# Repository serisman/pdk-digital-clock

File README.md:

# pdk-digital-clock
A 4-digit 7-segment digital clock, based on the inexpensive 8-bit Padauk microcontrollers

This project uses the [SLR0394DRC5BD](https://lcsc.com/product-detail/Led-Segment-Display_SUNLIGHT-SLR0394DRA5BD_C225902.html) 4-digit 7-segment common cathode 'time' display,
which sits over the top of a 74HC595 and (2) 4x resistor packs.
The 74HC595 is used to enable each of the four 7-segment digits, one at a time, using two output pins per digit for extra current sink capabilities.
The segments themselves are driven directly by the Port B outputs of the Padauk microcontroller.
Each of the four 7-segment digits is enabled and updated, one at a time, several 10's of times a second.

### Default Firmware (Push Button)
- Link: [Firmware](firmware/)

A single push button is used to set the time, with the following 'user interface':
- A short press will temporarily show the current 'seconds'.
- A medium-press will switch to time config mode.  While in config mode:
  - A short press will increment the currently selected time value, with rollover.
  - A medium-press will switch to the next time value, or exit config mode if on the last time value.
  - A long-press will exit config mode. 

### Alternate Firmware (Serial)
- Link: [Firmware-Serial](firmware-serial/)

This alternate firmware allows the time to be set by a serial command instead of requiring button presses.
This makes it easier to keep time updated and synced after it naturally drifts due to crystal accuracy and temperature fluctuations.

To set/update time, connect a Serial UART's TX pin (TTL level) to pin PA5 (PIN_RX):
- Send the following 5 bytes @9600 baud (1 start bit, 8 data bits, 1 stop bit, no parity):
    - `start byte`: 0x00
    - `hours byte`: using bcd notation, bit[7] is am_pm indicator, bits[5:4] is hours_10, bits[3:0] is hours_01
    - `minutes byte`: using bcd notation, bits[6:4] is minutes_10, bits[3:0] is minutes_01
    - `seconds byte`: using bcd notation, bits[6:4] is seconds_10, bits[3:0] is seconds_01
    - `checksum byte`: the sum of all preceding data bytes.

### Power Consumption

This digital clock is powered via micro USB cable, although it should work at much lower voltages as well.
It isn't really suitable for long-term battery operation, as the LED based 7-segment display consumes enough energy that the battery wouldn't last very long.

#### Power consumption (displaying 12:00):
- @ 5.0V = ~19mA
- @ 4.5V = ~16mA
- @ 4.0V = ~13mA
- @ 3.5V = ~10mA
- @ 3.0V = ~7mA
- @ 2.5V = ~4mA
- @ 2.0V = ~1mA

### PCB
- Design Files: [KiCad](pcb-s16/)
- Shared: [OSHPARK](https://oshpark.com/shared_projects/jvGgF1gC)

### Schematic
(for 16-pin PFS154, PFS173, PMS152, or PMS154C)
> 

### Compatibility
This project is currently intended to be run (without modifications) on the PFS154, PFS173, PMS152, and PMS154C Padauk microcontrollers,
but it should be able to be modified to run on other 16-pin Padauk microcontrollers that are supported by SDCC and the Easy PDK Programmer.

### Bill of Materials
| Ref | Part # | Description | Footprint | Purchase Link | Price | Minimum Purchase |
| --- | --- | --- | --- | --- | --- | --- |
| PCB | - | - | - | [OSHPARK](https://oshpark.com/shared_projects/jvGgF1gC) | $1.033 each | $3.10 for 3 |
| U3 | SLR0394DRA5BD | 4-digit time-mode 7-segment display | - | [LCSC C225902](https://lcsc.com/product-detail/Led-Segment-Display_SUNLIGHT-SLR0394DRA5BD_C225902.html) | $0.501 each | $0.501 for 1|  
| U1 | PMS152-S16 | 8-bit Padauk microcontroller | SOP-16 | [LCSC C317590](https://lcsc.com/product-detail/Others_PADAUK-Tech-PMS152-S16_C317590.html) | $0.077 each | $0.39 for 5 |
| U2 | 74HC595D | Serial shift register | SOP-16 | [LCSC C93838](https://lcsc.com/product-detail/LED-Drivers_Shenzhen-Sunmoon-Micro-SM74HC595D_C93838.html) | $0.046 each | $0.46 for 10 |
| Y1 | - | 32.767KHz radial cylinder crystal | 2x6mm | [LCSC C2236](https://lcsc.com/product-detail/Radial-Cylinder-Crystals_Yangxing-Tech-X206032768KGB2SC_C2236.html) | $0.045 each | $0.45 for 10 |
| J1 | - | Micro USB connector | - | [LCSC C393940](https://lcsc.com/product-detail/USB-Connectors_SHOU-HAN-MICRO5-9mmusb_C393940.html) | $0.026 each | $0.52 for 20 |   
| SW1 | TS24CA | SPST side-actuated button tactile switch | - | [LCSC C393942](https://lcsc.com/product-detail/Tactile-Switches_SHOU-HAN-TS24CA_C393942.html) | $0.025 each | $0.50 for 20 |
| C2 | - | 10uF capacitor | 0805 | [LCSC C92786](https://lcsc.com/product-detail/Multilayer-Ceramic-Capacitors-MLCC-SMD-SMT_Taiyo-Yuden_JMK212BJ106KD-T_Taiyo-Yuden-JMK212BJ106KD-T_C92786.html) | $0.015 each | $0.73 for 50 |
| C3,C4 | - | 20pF capacitor | 0805 | [LCSC C309037](https://lcsc.com/product-detail/Multilayer-Ceramic-Capacitors-MLCC-SMD-SMT_CCTC-TCC0805C0G200J500BT_C309037.html) | $0.007 each | $0.36 for 50 |
| RN1,RN2 | - | 4x 680 ohm resistor network | 0603_x4 | [LCSC C102679](https://lcsc.com/product-detail/Resistor-Networks-Arrays_RALEC-RTA03-4D681JTP_C102679.html) | $0.007 each | $0.35 for 50 |
| C1 | - | 100nF capacitor | 0805 | [LCSC C235732](https://lcsc.com/product-detail/Multilayer-Ceramic-Capacitors-MLCC-SMD-SMT_PSA-Prosperity-Dielectrics-FN21X104K500PXG_C235732.html) | $0.006 each | $0.30 for 50 |

Total: ~$1.80 each (+/- depending on quantity)

### Images
.jpg?raw=true)

### Copyright and License:
- Copyright (C) 2020 - serisman (github@serisman.com)
- License: [GPL v3 (or later)](LICENSE)

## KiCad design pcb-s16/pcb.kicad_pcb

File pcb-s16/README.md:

# pcb-s16 ([pdk-digital-clock](https://github.com/serisman/pdk-digital-clock/))

### Schematic
(for 16-pin PFS154, PFS173, PMS152, or PMS154C)
> 

### PCB

This PCB design was created with KiCad, and has been [shared on OSHPARK](https://oshpark.com/shared_projects/jvGgF1gC).
There are also gerber files available in the [output/gerber/](output/gerber/) directory.

This uses the [SLR0394DRC5BD](https://lcsc.com/product-detail/Led-Segment-Display_SUNLIGHT-SLR0394DRA5BD_C225902.html) 4-digit 7-segment common cathode 'time' display,
which sits over the top of the 74HC595 and the (2) 4x resistor packs.
The 74HC595 is used to drive the (4) 7-segment digits, (2) outputs per digit for extra current sink capabilities.
The segments themselves are driven directly by the Port B outputs of the Padauk microcontroller.

A single push button is used to set the time, with the following 'user interface':
- A short press will temporarily show the current 'seconds'.
- A medium-press will switch to time config mode.  While in config mode:
  - A short press will increment the currently selected time value, with rollover.
  - A medium-press will switch to the next time value, or exit config mode if on the last time value.
  - A long-press will exit config mode. 

This digital clock is powered via micro USB cable, although it should work at much lower voltages as well.
It isn't really suitable for long-term battery operation, as the LED based 7-segment display consumes enough energy that it wouldn't last very long.

### Bill of Materials
| Ref | Part # | Description | Footprint | Purchase Link | Price | Minimum Purchase |
| --- | --- | --- | --- | --- | --- | --- |
| PCB | - | - | - | [OSHPARK](https://oshpark.com/shared_projects/jvGgF1gC) | $1.033 each | $3.10 for 3 |
| U3 | SLR0394DRA5BD | 4-digit time-mode 7-segment display | - | [LCSC C225902](https://lcsc.com/product-detail/Led-Segment-Display_SUNLIGHT-SLR0394DRA5BD_C225902.html) | $0.501 each | $0.501 for 1|  
| U1 | PMS152-S16 | 8-bit Padauk microcontroller | SOP-16 | [LCSC C317590](https://lcsc.com/product-detail/Others_PADAUK-Tech-PMS152-S16_C317590.html) | $0.077 each | $0.39 for 5 |
| U2 | 74HC595D | Serial shift register | SOP-16 | [LCSC C93838](https://lcsc.com/product-detail/LED-Drivers_Shenzhen-Sunmoon-Micro-SM74HC595D_C93838.html) | $0.046 each | $0.46 for 10 |
| Y1 | - | 32.767KHz radial cylinder crystal | 2x6mm | [LCSC C2236](https://lcsc.com/product-detail/Radial-Cylinder-Crystals_Yangxing-Tech-X206032768KGB2SC_C2236.html) | $0.045 each | $0.45 for 10 |
| J1 | - | Micro USB connector | - | [LCSC C393940](https://lcsc.com/product-detail/USB-Connectors_SHOU-HAN-MICRO5-9mmusb_C393940.html) | $0.026 each | $0.52 for 20 |   
| SW1 | TS24CA | SPST side-actuated button tactile switch | - | [LCSC C393942](https://lcsc.com/product-detail/Tactile-Switches_SHOU-HAN-TS24CA_C393942.html) | $0.025 each | $0.50 for 20 |
| C2 | - | 10uF capacitor | 0805 | [LCSC C92786](https://lcsc.com/product-detail/Multilayer-Ceramic-Capacitors-MLCC-SMD-SMT_Taiyo-Yuden_JMK212BJ106KD-T_Taiyo-Yuden-JMK212BJ106KD-T_C92786.html) | $0.015 each | $0.73 for 50 |
| C3,C4 | - | 20pF capacitor | 0805 | [LCSC C309037](https://lcsc.com/product-detail/Multilayer-Ceramic-Capacitors-MLCC-SMD-SMT_CCTC-TCC0805C0G200J500BT_C309037.html) | $0.007 each | $0.36 for 50 |
| RN1,RN2 | - | 4x 680 ohm resistor network | 0603_x4 | [LCSC C102679](https://lcsc.com/product-detail/Resistor-Networks-Arrays_RALEC-RTA03-4D681JTP_C102679.html) | $0.007 each | $0.35 for 50 |
| C1 | - | 100nF capacitor | 0805 | [LCSC C235732](https://lcsc.com/product-detail/Multilayer-Ceramic-Capacitors-MLCC-SMD-SMT_PSA-Prosperity-Dielectrics-FN21X104K500PXG_C235732.html) | $0.006 each | $0.30 for 50 |

Total: ~$1.80 each (+/- depending on quantity)

### PCB Renders

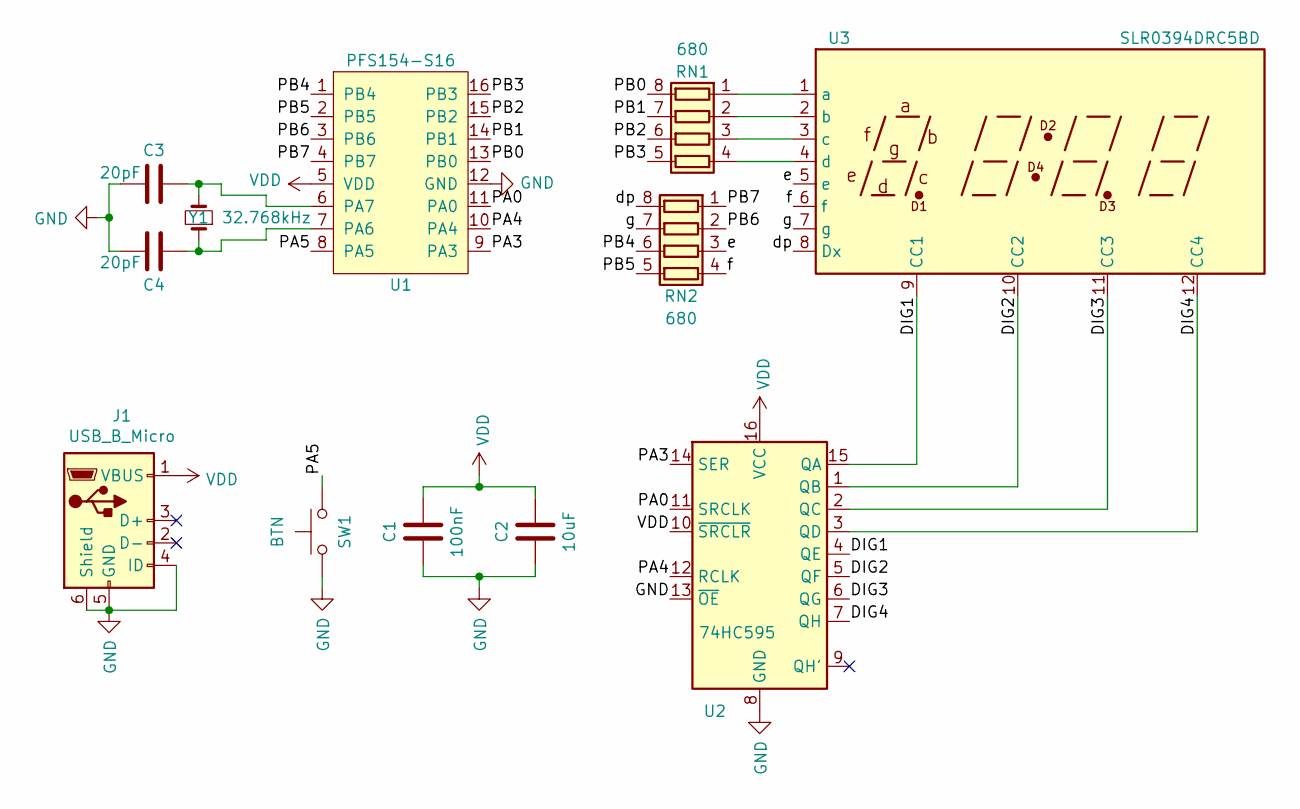
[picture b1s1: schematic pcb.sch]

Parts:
C1: 100nF; C_0805
C2: 10uF; C_0805
C3, C4: 20pF; C_0805
J1: USB_B_Micro; USB_Micro_B_Male
RN1, RN2: 680; R_Array_Convex_4x0603
SW1: BTN; SMD-SW_Push_3.5x4.55_Side
U1: PFS154-S16; SOIC-16_3.9x9.9mm_P1.27mm
U2: 74HC595; SOIC-16_3.9x9.9mm_P1.27mm
U3: SLR0394DRC5BD; SLR039DRC5BD
Y1: 32.768kHz; Crystal_C26-LF_D2.1mm_L6.5mm_Horizontal

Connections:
/DIG1: U2.4 (QE), U2.15 (QA), U3.9 (CC1)
/DIG2: U2.1 (QB), U2.5 (QF), U3.10 (CC2)
/DIG3: U2.2 (QC), U2.6 (QG), U3.11 (CC3)
/DIG4: U2.3 (QD), U2.7 (QH), U3.12 (CC4)
/PA0: U1.11 (PA0), U2.11 (SRCLK)
/PA3: U1.9 (PA3), U2.14 (SER)
/PA4: U1.10 (PA4), U2.12 (RCLK)
/PA5: SW1.2, U1.8 (PA5)
/PB0: RN1.8 (R1.2), U1.13 (PB0)
/PB1: RN1.7 (R2.2), U1.14 (PB1)
/PB2: RN1.6 (R3.2), U1.15 (PB2)
/PB3: RN1.5 (R4.2), U1.16 (PB3)
/PB4: RN2.6 (R3.2), U1.1 (PB4)
/PB5: RN2.5 (R4.2), U1.2 (PB5)
/PB6: RN2.2 (R2.1), U1.3 (PB6)
/PB7: RN2.1 (R1.1), U1.4 (PB7)
/dp: RN2.8 (R1.2), U3.8 (Dx)
/e: RN2.3 (R3.1), U3.5 (e)
/f: RN2.4 (R4.1), U3.6 (f)
/g: RN2.7 (R2.2), U3.7 (g)
GND: C1.2, C2.2, C3.1, C4.1, J1.4 (ID), J1.5 (GND), J1.6 (Shield), SW1.1, SW1.SH, U1.12 (GND), U2.8 (GND), U2.13 (~OE)
unnamed: C3.2, U1.6 (PA7), Y1.2
unnamed: C4.2, U1.7 (PA6), Y1.1
unnamed: RN1.1 (R1.1), U3.1 (a)
unnamed: RN1.2 (R2.1), U3.2 (b)
unnamed: RN1.3 (R3.1), U3.3 (c)
unnamed: RN1.4 (R4.1), U3.4 (d)
VDD: C1.1, C2.1, J1.1 (VBUS), U1.5 (VDD), U2.10 (~SRCLR), U2.16 (VCC)

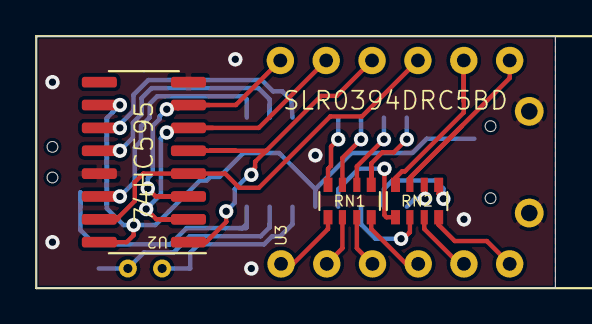
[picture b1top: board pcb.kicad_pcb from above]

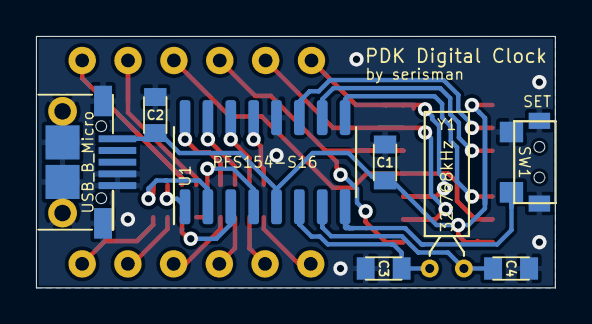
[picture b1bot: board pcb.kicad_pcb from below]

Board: 2 copper layers, 28.8 x 14.0 mm, 12 parts (8 on the bottom side), 28 nets.

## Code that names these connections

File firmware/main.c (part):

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//
//  Assumes (#define'd above):
//   Segments[a-g,dp] are mapped to PB[0-7]
//   74HC595 (14) DS - DATA is on PA3
//   74HC595 (11) SH_CP - CLOCK is on PA0
//   74HC595 (12) ST_CP - LATCH is on PA4
void display_next_digit(void) {
__asm
	;// Rotate to next digit
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
// Main program
void main(void) {
  // Make sure PA7/PA6 is Disabled for External Crystal (recommended for all ICs)
  // Make sure PA5 is Enabled as input for Button (needed by PMS152/PFS173)
  PADIER = 0b00100000;

	// Set appropriate pins as outputs (all pins are input by default)
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
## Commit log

2020-07-17 Initial Version
2020-07-17 Add PCB files and renders
2020-07-19 Update schematic
2020-07-19 Add schematic to README.md
2020-07-19 Create LICENSE
2020-07-20 Add firmware (move from old Padauk repository)
2020-07-20 Add README.md for the PCB
2020-07-24 Update Crystal
2020-08-01 Add values (680 ohm) for resistor arrays
2020-08-01 Add finished images, and Bill-of-materials
2020-08-01 Tweak bill of materials
2020-08-01 Update comment
2022-06-29 Add some power consumption numbers
2022-09-08 fix PFS173
2025-07-18 Fixes for newer version of SDCC
2025-07-19 Minor tweaks after SDCC upgrade
2025-07-19 Add alternate firmware-serial
2025-07-19 rename parity to checksum
2025-11-17 Add support for alternate digit pin layout
2025-11-17 Add support for another alternate digit pin layout that has separate blink segment pins.
2025-11-17 Fix incomplete rename.

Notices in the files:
firmware/main.c:
This program is free software: you can redistribute it and/or modify
it under the terms of the GNU General Public License as published by
the Free Software Foundation, either version 3 of the License, or
(at your option) any later version.
